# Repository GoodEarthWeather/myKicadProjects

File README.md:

# myKicadProjects
 Kicad Schematic and PCB Projects

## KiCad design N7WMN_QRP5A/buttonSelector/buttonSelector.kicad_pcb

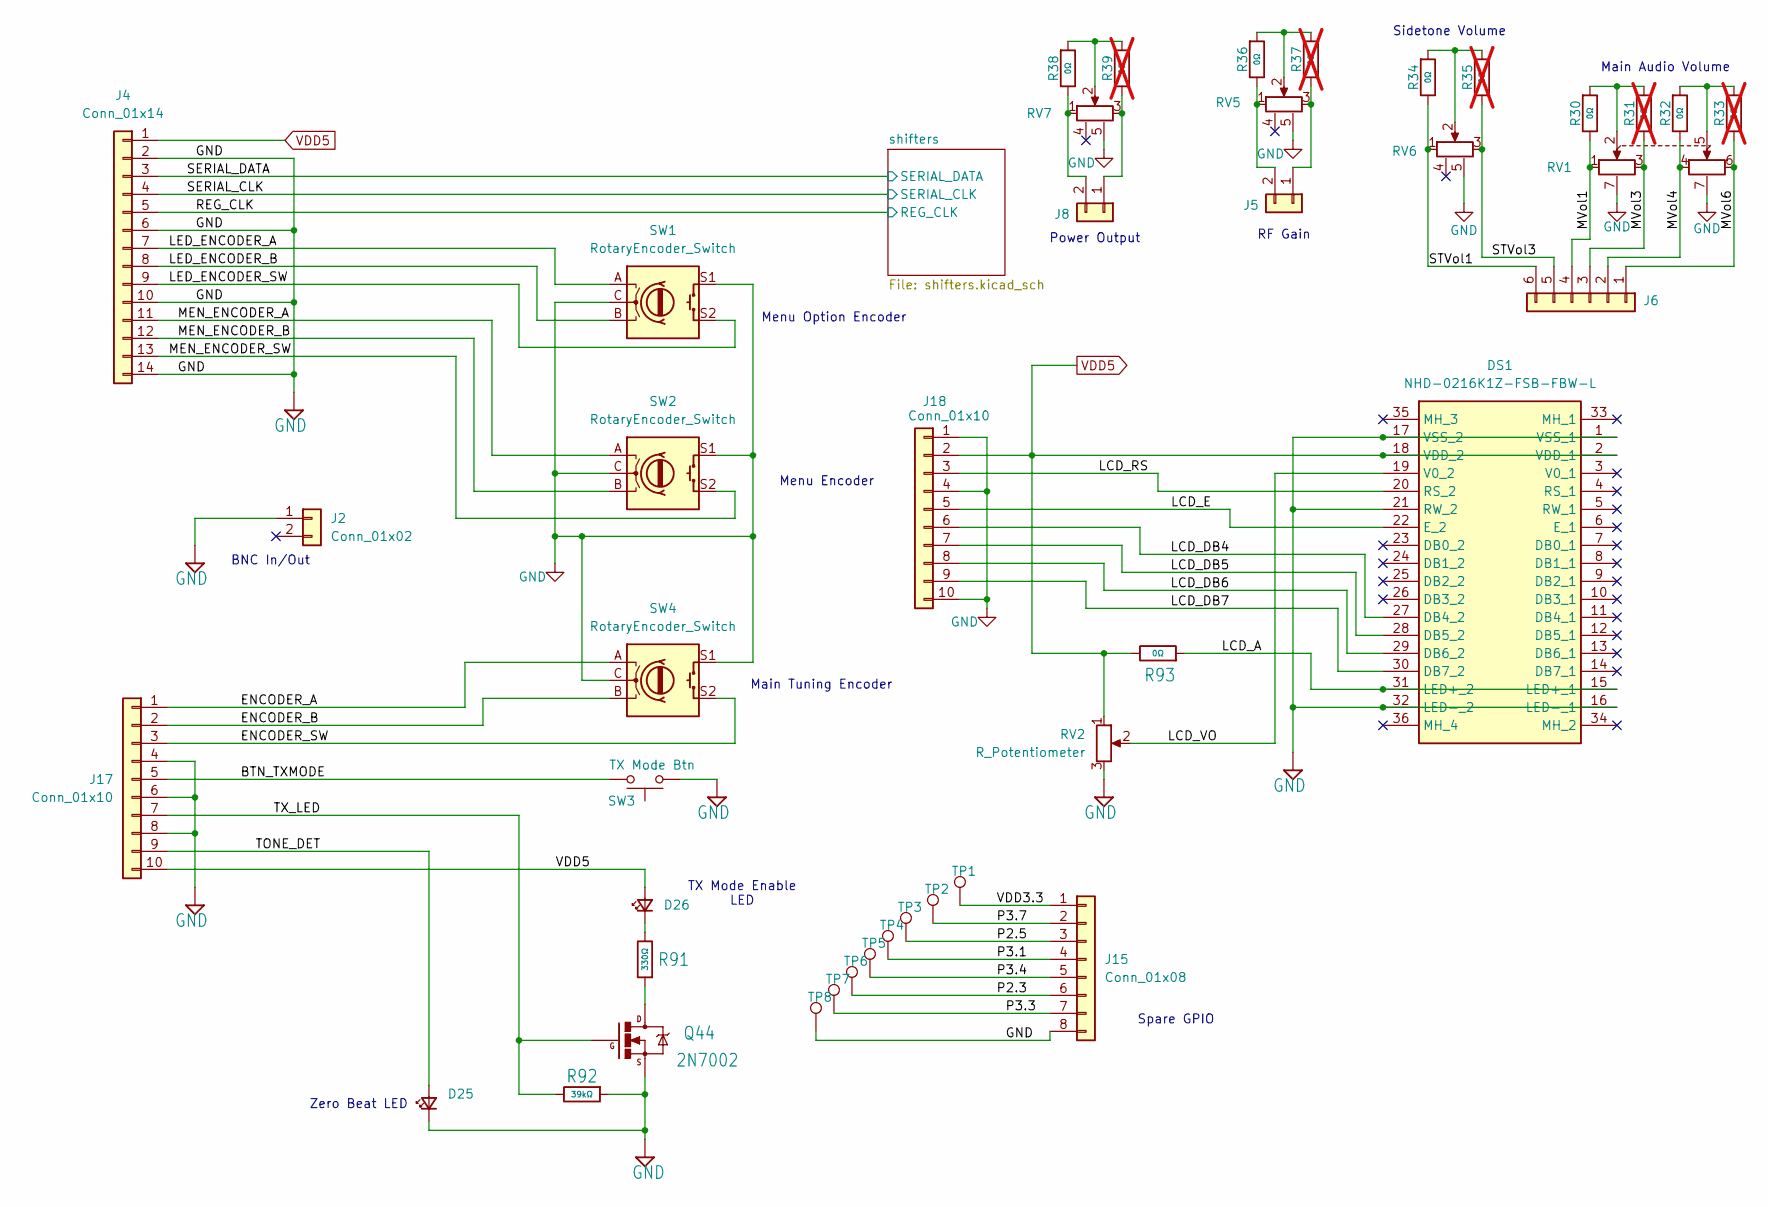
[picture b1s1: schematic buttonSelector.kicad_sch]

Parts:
D25, D26: LED_Small; LED_D5.0mm; MouserPN 606-CMD333URC2
DS1: NHD-0216K1Z-FSB-FBW-L; NHD0216K1ZFSBFBWL; Mouser Part Number 763-0216K1Z-FSB-FBW
J2, J5, J8: Conn_01x02; PinHeader_1x02_P2.54mm_Vertical
J4: Conn_01x14; PinHeader_1x14_P2.54mm_Vertical
J6: Conn_01x06; PinHeader_1x06_P2.54mm_Vertical
J15: Conn_01x08; PinHeader_1x08_P2.54mm_Vertical
J17, J18: Conn_01x10; PinHeader_1x10_P2.54mm_Vertical
Q44: 2N7002; SOT-23; JLCPCB C65189
R30, R32, R34, R36, R38, R93: 0Ω; R_0603; Overload Voltage (Max) 75V; Tolerance ±1%; Part 0603WAF0000T5E; LCSC C21189
R31, R33, R35, R37, R39: 0Ω; R_0603; Overload Voltage (Max) 75V; Tolerance ±1%; Part 0603WAF0000T5E; LCSC C21189; not fitted
R91: 330Ω; R_0603; Overload Voltage (Max) 75V; Tolerance ±1%; Part 0603WAF3300T5E; LCSC C23138
R92: 39kΩ; R_0603; Overload Voltage (Max) 75V; Tolerance ±1%; Part 0603WAF3902T5E; LCSC C23153
RV1: R_Potentiometer_Dual; PVT112-4_Potentiometer; Mouser Part Number 652-PTV112-4420AA103
RV2: R_Potentiometer; Potentiometer_Bourns_3386C_Horizontal
RV5: R_Potentiometer_PVT111; PVT111-4_Potentiometer; Mouser Part Number 652-PTV111-4420AB503
RV6: R_Potentiometer_PVT111; PVT111-4_Potentiometer; Mouser Part Number 652-PTV111-4420AA502
RV7: R_Potentiometer_PVT111; PVT111-4_Potentiometer; Mouser Part Number 652-PTV111-4420AB502
SW1, SW2: RotaryEncoder_Switch; RotaryEncoder_Alps_EC11E-Switch_Vertical_H20mm; Mouser Part Number 652-PEC11R-4220F-S24
SW3: TX Mode Btn; SW_PUSH-12mm
SW4: RotaryEncoder_Switch; RotaryEncoder_Alps_EC11E-Switch_Vertical_H20mm; Mouser Part Number 652-PEC11R-4020F-S24
TP1, TP2, TP3, TP4, TP5, TP6, TP7, TP8: TestPoint; TestPoint_Loop_D2.50mm_Drill1.0mm

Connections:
/BTN_TXMODE: J17.5, SW3.2
/ENCODER_A: J17.1, SW4.A
/ENCODER_B: J17.2, SW4.B
/ENCODER_SW: J17.3, SW4.S2
/LCD_A: DS1.15 (LED+_1), DS1.31 (LED+_2), R93.1
/LCD_DB4: DS1.27 (DB4_2), J18.6
/LCD_DB5: DS1.28 (DB5_2), J18.7
/LCD_DB6: DS1.29 (DB6_2), J18.8
/LCD_DB7: DS1.30 (DB7_2), J18.9
/LCD_E: DS1.22 (E_2), J18.5
/LCD_RS: DS1.20 (RS_2), J18.3
/LCD_VO: DS1.19 (V0_2), RV2.2
/LED_ENCODER_A: J4.7, SW1.A
/LED_ENCODER_B: J4.8, SW1.B
/LED_ENCODER_SW: J4.9, SW1.S2
/MEN_ENCODER_A: J4.11, SW2.A
/MEN_ENCODER_B: J4.12, SW2.B
/MEN_ENCODER_SW: J4.13, SW2.S2
/MVol1: J6.4, R30.2, RV1.1
/MVol3: J6.3, R31.2, RV1.3
/MVol4: J6.2, R32.2, RV1.4
/MVol6: J6.1, R33.2, RV1.6
/P2.3: J15.6, TP6.1 (1_1)
/P2.5: J15.3, TP3.1 (1_1)
/P3.1: J15.4, TP4.1 (1_1)
/P3.3: J15.7, TP7.1 (1_1)
/P3.4: J15.5, TP5.1 (1_1)
/P3.7: J15.2, TP2.1 (1_1)
/REG_CLK: J4.5; also elsewhere on the board
/SERIAL_CLK: J4.4; also elsewhere on the board
/SERIAL_DATA: J4.3; also elsewhere on the board
/STVol1: J6.6, R34.2, RV6.1
/STVol3: J6.5, R35.2, RV6.3
/TONE_DET: D25.2 (A), J17.9
/TX_LED: J17.7, Q44.1 (G), R92.2
/VDD3.3: J15.1, TP1.1 (1_1)
GND: D25.1 (K), DS1.1 (VSS_1), DS1.16 (LED-_1), DS1.17 (VSS_2), DS1.21 (RW_2), DS1.32 (LED-_2), J2.1 (Pin_1_1), J4.2, J4.6, J4.10, J4.14, J15.8, J17.4, J17.6, J17.8, J18.1, J18.4, J18.10, Q44.2 (S), R92.1, RV1.7 (NC), RV2.3, RV5.5 (gnd), RV6.5 (gnd), RV7.5 (gnd), SW1.C, SW1.S1, SW2.C, SW2.S1, SW3.1, SW4.C, SW4.S1, TP8.1 (1_1); also elsewhere on the board
unnamed: D26.1 (K), R91.2
unnamed: J5.1, R37.2, RV5.3
unnamed: J5.2, R36.2, RV5.1
unnamed: J8.1, R39.2, RV7.3
unnamed: J8.2, R38.2, RV7.1
unnamed: Q44.3 (D), R91.1
unnamed: R30.1, R31.1, RV1.2
unnamed: R32.1, R33.1, RV1.5
unnamed: R34.1, R35.1, RV6.2
unnamed: R36.1, R37.1, RV5.2
unnamed: R38.1, R39.1, RV7.2
VDD5: D26.2 (A), DS1.2 (VDD_1), DS1.18 (VDD_2), J4.1, J17.10, J18.2, R93.2, RV2.1; also elsewhere on the board

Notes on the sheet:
Main Tuning Encoder
Menu Encoder
Menu Option Encoder
BNC In/Out
Sidetone Volume
RF Gain
Main Audio Volume
TX Mode Enable LED
Power Output
Spare GPIO
Zero Beat LED

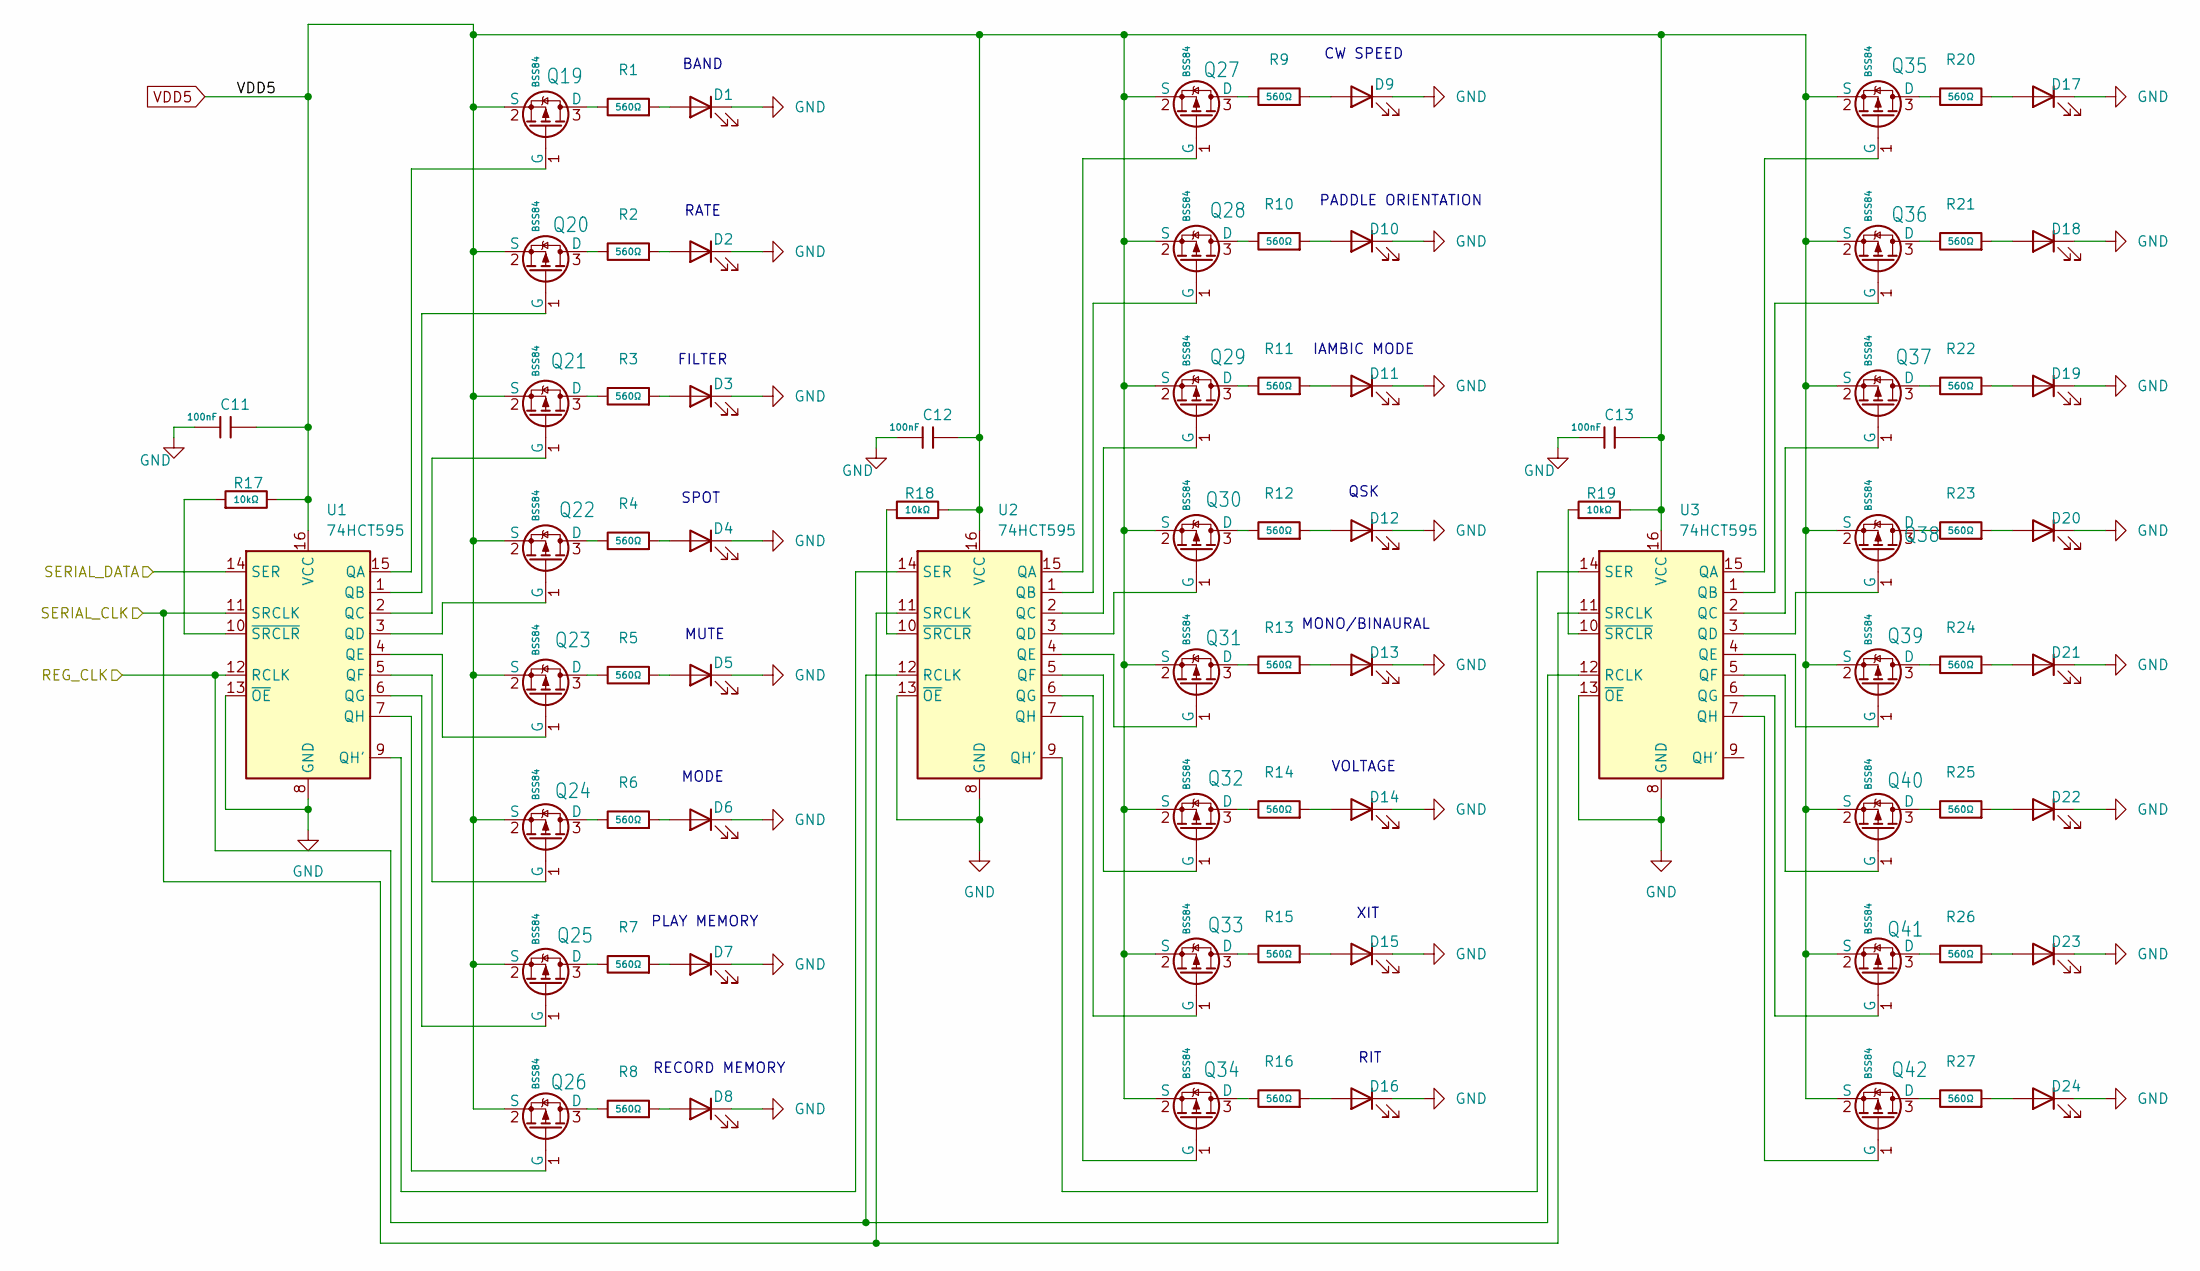
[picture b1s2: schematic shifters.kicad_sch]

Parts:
C11, C12, C13: 100nF; C_0603; Voltage Rated 50V; Tolerance ±10%; Part CC0603KRX7R9BB104; LCSC C14663
D1, D2, D3, D4, D5, D6, D7, D8, D9, D10, D11, D12, D13, D14, D15, D16, D17, D18, D19, D20, D21, D22, D23, D24: LED; LED_D5.0mm_Clear; Mouser Part Number 606-CMD333URC2
Q19, Q20, Q21, Q22, Q23, Q24, Q25, Q26, Q27, Q28, Q29, Q30, Q31, Q32, Q33, Q34, Q35, Q36, Q37, Q38, Q39, Q40, Q41, Q42: BSS84; Q_SOT-23; Part BSS84; JLCPCB C65189
R1, R2, R3, R4, R5, R6, R7, R8, R9, R10, R11, R12, R13, R14, R15, R16, R20, R21, R22, R23, R24, R25, R26, R27: 560Ω; R_0603; Overload Voltage (Max) 75V; Tolerance ±1%; Part 0603WAF5600T5E; JLCPCB C23204
R17, R18, R19: 10kΩ; R_0603; Overload Voltage (Max) 75V; Tolerance ±1%; Part 0603WAF1002T5E; LCSC C25804
U1, U2, U3: 74HCT595; TSSOP-16_4.4x5mm_P0.65mm; JLCPCB C3304571

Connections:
/REG_CLK: U1.12 (RCLK), U2.12 (RCLK), U3.12 (RCLK); also elsewhere on the board
/SERIAL_CLK: U1.11 (SRCLK), U2.11 (SRCLK), U3.11 (SRCLK); also elsewhere on the board
/SERIAL_DATA: U1.14 (SER); also elsewhere on the board
GND: C11.2, C12.2, C13.2, D1.1 (K), D2.1 (K), D3.1 (K), D4.1 (K), D5.1 (K), D6.1 (K), D7.1 (K), D8.1 (K), D9.1 (K), D10.1 (K), D11.1 (K), D12.1 (K), D13.1 (K), D14.1 (K), D15.1 (K), D16.1 (K), D17.1 (K), D18.1 (K), D19.1 (K), D20.1 (K), D21.1 (K), D22.1 (K), D23.1 (K), D24.1 (K), U1.8 (GND), U1.13 (~OE), U2.8 (GND), U2.13 (~OE), U3.8 (GND), U3.13 (~OE); also elsewhere on the board
unnamed: D1.2 (A), R1.1
unnamed: D2.2 (A), R2.1
unnamed: D3.2 (A), R3.1
unnamed: D4.2 (A), R4.1
unnamed: D5.2 (A), R5.1
unnamed: D6.2 (A), R6.1
unnamed: D7.2 (A), R7.1
unnamed: D8.2 (A), R8.1
unnamed: D9.2 (A), R9.1
unnamed: D10.2 (A), R10.1
unnamed: D11.2 (A), R11.1
unnamed: D12.2 (A), R12.1
unnamed: D13.2 (A), R13.1
unnamed: D14.2 (A), R14.1
unnamed: D15.2 (A), R15.1
unnamed: D16.2 (A), R16.1
unnamed: D17.2 (A), R20.1
unnamed: D18.2 (A), R21.1
unnamed: D19.2 (A), R22.1
unnamed: D20.2 (A), R23.1
unnamed: D21.2 (A), R24.1
unnamed: D22.2 (A), R25.1
unnamed: D23.2 (A), R26.1
unnamed: D24.2 (A), R27.1
unnamed: Q19.3 (D), R1.2
unnamed: Q19.1 (G), U1.15 (QA)
unnamed: Q20.3 (D), R2.2
unnamed: Q20.1 (G), U1.1 (QB)
unnamed: Q21.3 (D), R3.2
unnamed: Q21.1 (G), U1.2 (QC)
unnamed: Q22.3 (D), R4.2
unnamed: Q22.1 (G), U1.3 (QD)
unnamed: Q23.3 (D), R5.2
unnamed: Q23.1 (G), U1.4 (QE)
unnamed: Q24.3 (D), R6.2
unnamed: Q24.1 (G), U1.5 (QF)
unnamed: Q25.3 (D), R7.2
unnamed: Q25.1 (G), U1.6 (QG)
unnamed: Q26.3 (D), R8.2
unnamed: Q26.1 (G), U1.7 (QH)
unnamed: Q27.3 (D), R9.2
unnamed: Q27.1 (G), U2.15 (QA)
unnamed: Q28.3 (D), R10.2
unnamed: Q28.1 (G), U2.1 (QB)
unnamed: Q29.3 (D), R11.2
unnamed: Q29.1 (G), U2.2 (QC)
unnamed: Q30.3 (D), R12.2
unnamed: Q30.1 (G), U2.3 (QD)
unnamed: Q31.3 (D), R13.2
unnamed: Q31.1 (G), U2.4 (QE)
unnamed: Q32.3 (D), R14.2
unnamed: Q32.1 (G), U2.5 (QF)
unnamed: Q33.3 (D), R15.2
unnamed: Q33.1 (G), U2.6 (QG)
unnamed: Q34.3 (D), R16.2
unnamed: Q34.1 (G), U2.7 (QH)
unnamed: Q35.3 (D), R20.2
unnamed: Q35.1 (G), U3.15 (QA)
unnamed: Q36.3 (D), R21.2
unnamed: Q36.1 (G), U3.1 (QB)
unnamed: Q37.3 (D), R22.2
unnamed: Q37.1 (G), U3.2 (QC)
unnamed: Q38.3 (D), R23.2
unnamed: Q38.1 (G), U3.3 (QD)
unnamed: Q39.3 (D), R24.2
unnamed: Q39.1 (G), U3.4 (QE)
unnamed: Q40.3 (D), R25.2
unnamed: Q40.1 (G), U3.5 (QF)
unnamed: Q41.3 (D), R26.2
unnamed: Q41.1 (G), U3.6 (QG)
unnamed: Q42.3 (D), R27.2
unnamed: Q42.1 (G), U3.7 (QH)
unnamed: U1.9 (QH'), U2.14 (SER)
unnamed: R17.1, U1.10 (~SRCLR)
unnamed: U2.9 (QH'), U3.14 (SER)
unnamed: R18.1, U2.10 (~SRCLR)
unnamed: R19.1, U3.10 (~SRCLR)
VDD5: C11.1, C12.1, C13.1, Q19.2 (S), Q20.2 (S), Q21.2 (S), Q22.2 (S), Q23.2 (S), Q24.2 (S), Q25.2 (S), Q26.2 (S), Q27.2 (S), Q28.2 (S), Q29.2 (S), Q30.2 (S), Q31.2 (S), Q32.2 (S), Q33.2 (S), Q34.2 (S), Q35.2 (S), Q36.2 (S), Q37.2 (S), Q38.2 (S), Q39.2 (S), Q40.2 (S), Q41.2 (S), Q42.2 (S), R17.2, R18.2, R19.2, U1.16 (VCC), U2.16 (VCC), U3.16 (VCC); also elsewhere on the board

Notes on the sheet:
MONO/BINAURAL
PLAY MEMORY
MUTE
QSK
RECORD MEMORY
SPOT
VOLTAGE
FILTER
BAND
RATE
IAMBIC MODE
RIT
MODE
PADDLE ORIENTATION
XIT
CW SPEED

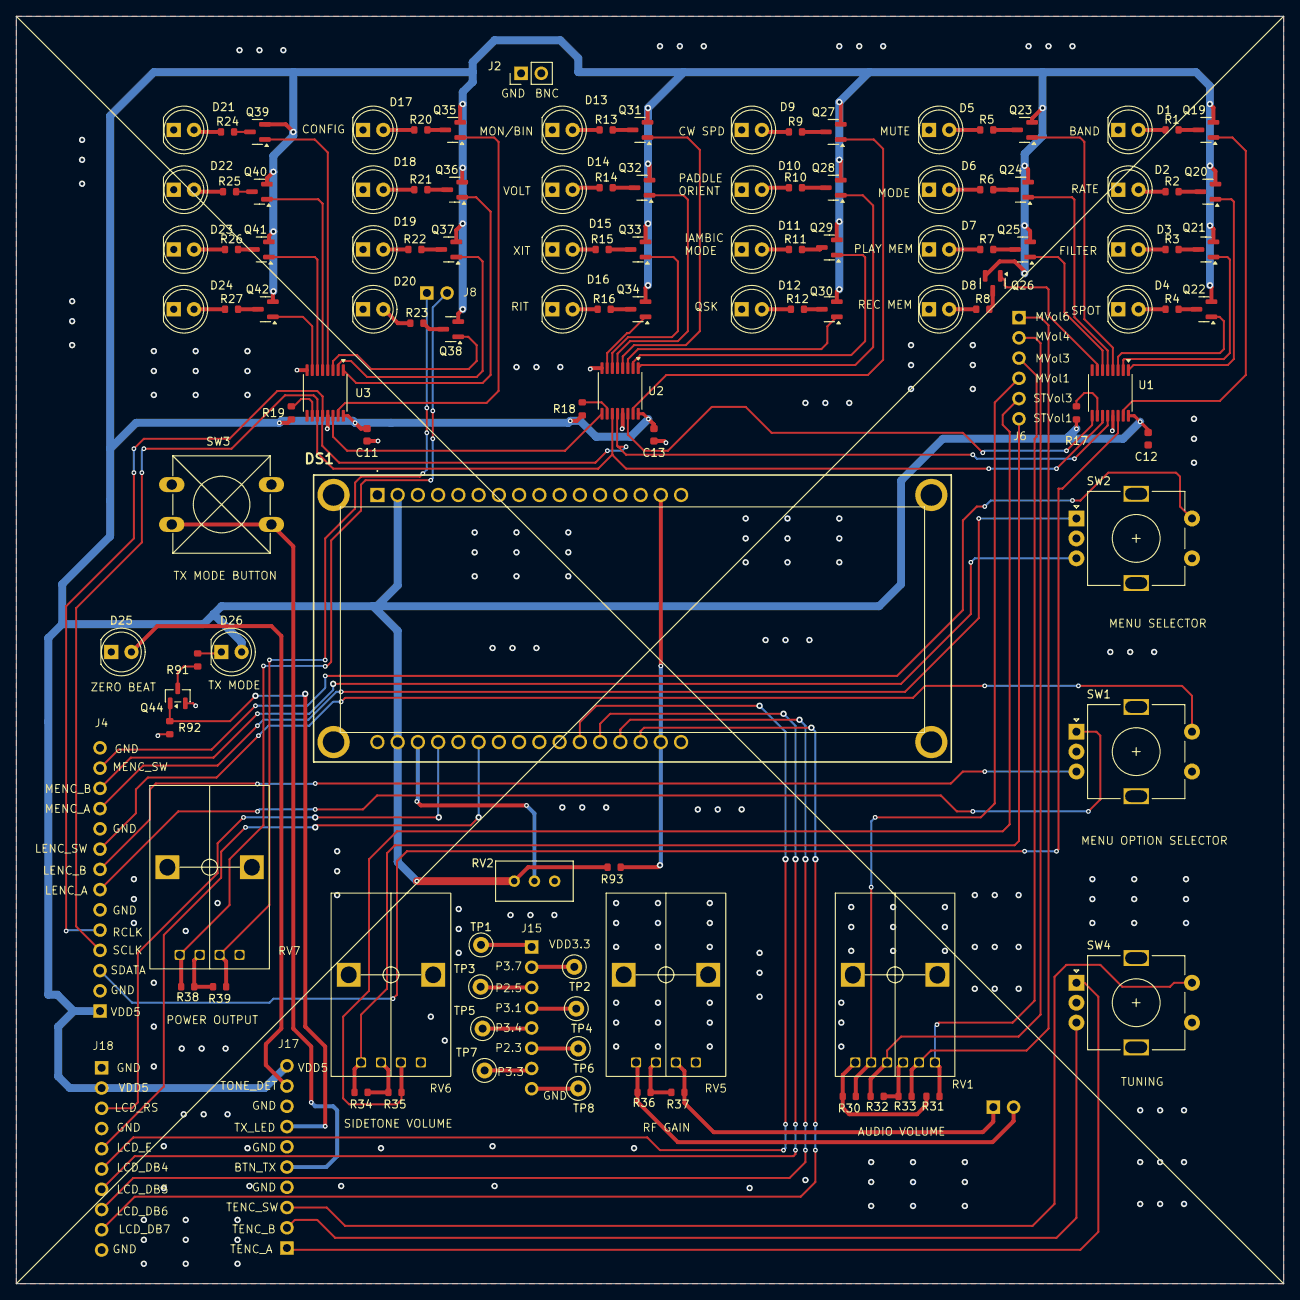
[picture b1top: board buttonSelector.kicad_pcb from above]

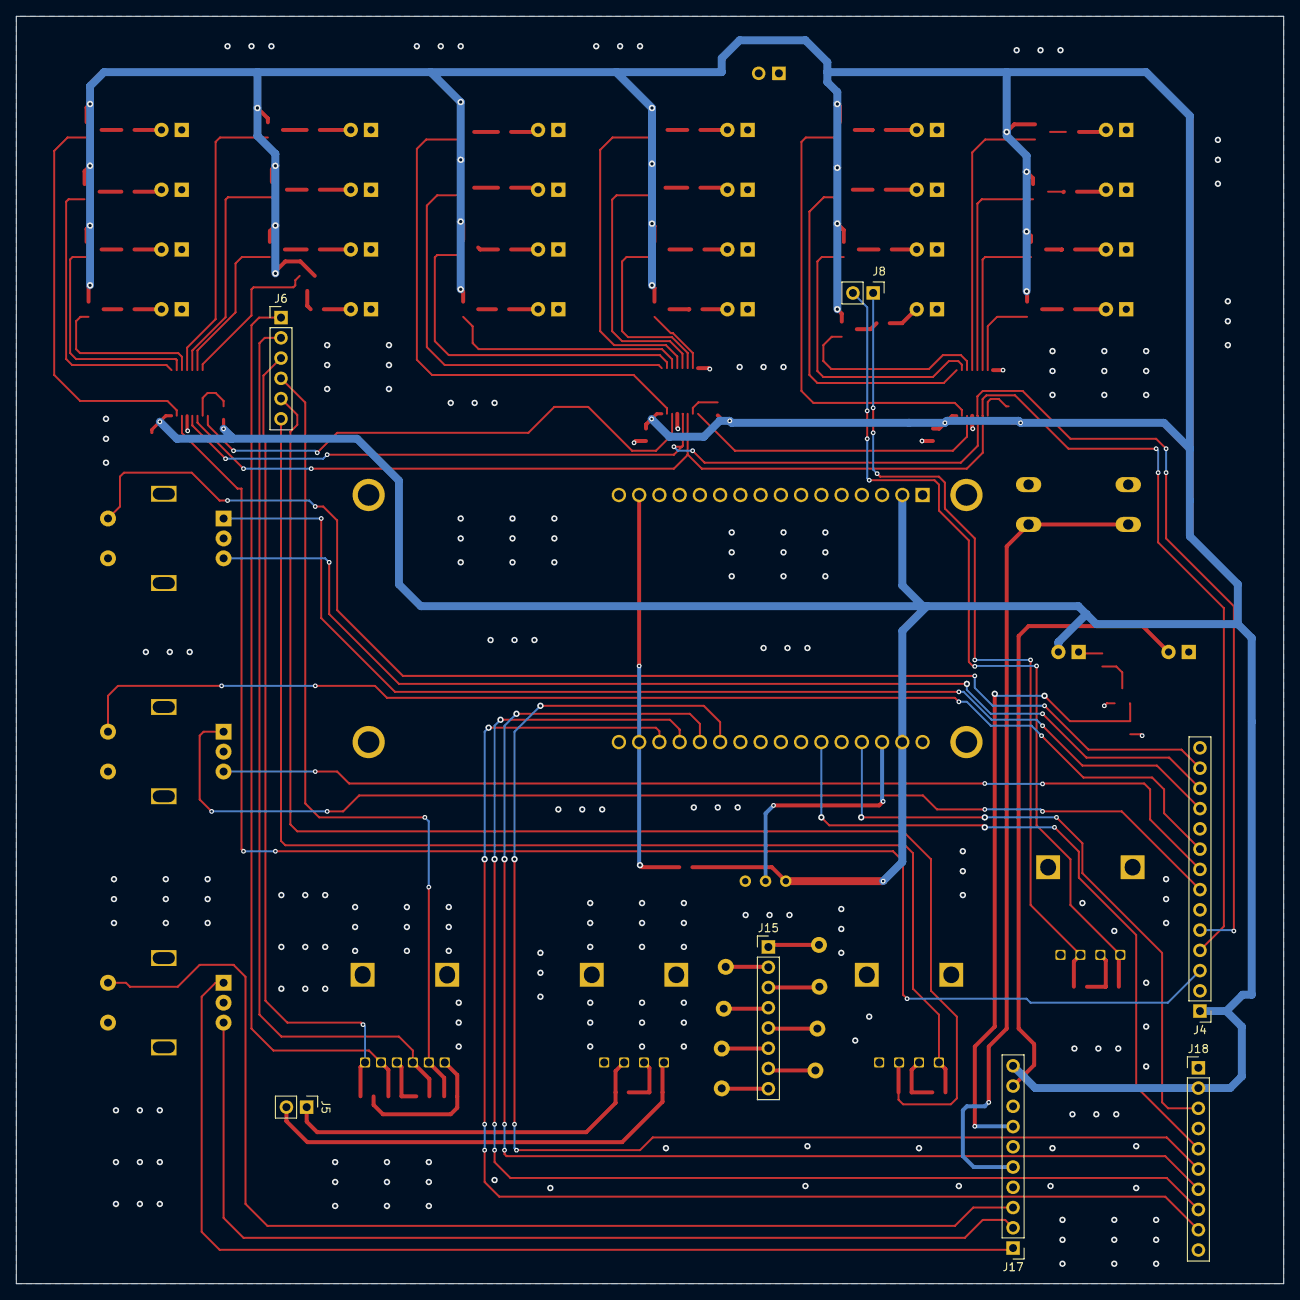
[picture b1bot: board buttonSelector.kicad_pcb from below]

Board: 2 copper layers, 159.0 x 159.0 mm, 123 parts (7 on the bottom side), 126 nets.

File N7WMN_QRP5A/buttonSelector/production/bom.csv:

Designator,Footprint,Quantity,Value,LCSC Part #
"C11, C12, C13",C_0603,3,100nF,C14663
"Q19, Q20, Q21, Q22, Q23, Q24, Q25, Q26, Q27, Q28, Q29, Q30, Q31, Q32, Q33, Q34, Q35, Q36, Q37, Q38, Q39, Q40, Q41, Q42",Q_SOT-23,24,BSS84,C7420340
Q44,SOT-23,1,2N7002,C65189
"R1, R10, R11, R12, R13, R14, R15, R16, R2, R20, R21, R22, R23, R24, R25, R26, R27, R3, R4, R5, R6, R7, R8, R9",R_0603,24,560Ω,C23204
"R17, R18, R19",R_0603,3,10kΩ,C25804
"R30, R31, R32, R33, R34, R35, R36, R37, R38, R39, R93",R_0603,11,0Ω,C21189
R91,R_0603,1,330Ω,C23138
R92,R_0603,1,39kΩ,C23153
"U1, U2, U3",TSSOP-16_4.4x5mm_P0.65mm,3,74HCT595,C3304571

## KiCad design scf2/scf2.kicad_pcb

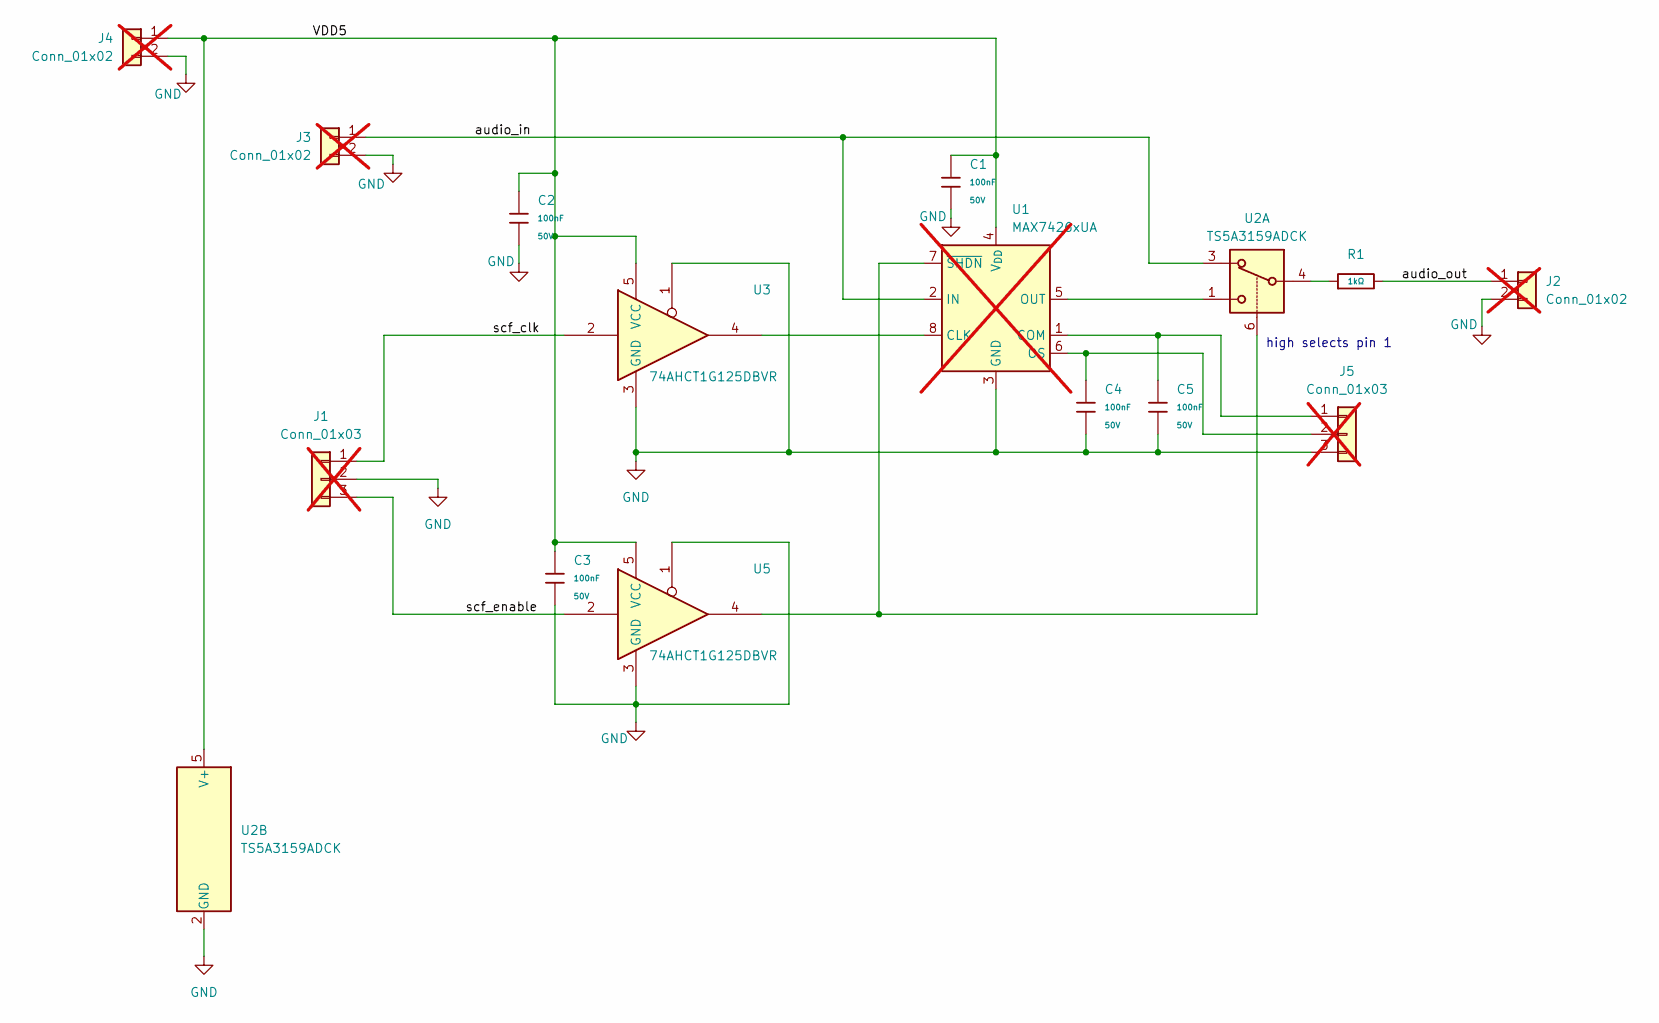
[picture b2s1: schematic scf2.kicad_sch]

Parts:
C1, C2, C3, C4, C5: 100nF; C_0603; Voltage Rated 50V; Tolerance ±10%; Part CC0603KRX7R9BB104; LCSC C14663
J1, J5: Conn_01x03; PinHeader_1x03_P2.54mm_Vertical; not fitted
J2, J3, J4: Conn_01x02; PinHeader_1x02_P2.54mm_Vertical; not fitted
R1: 1kΩ; R_0603; Overload Voltage (Max) 75V; Tolerance ±1%; Part 0603WAF1001T5E; LCSC C21190
U1: MAX7426xUA; MSOP-8_3x3mm_P0.65mm; jlcpcb C17445855; not fitted
U2: TS5A3159ADCK; SOT-363_SC-70-6; jlcpcb C475493
U3, U5: 74AHCT1G125DBVR; SOT-23-5_HandSoldering; jlcpcb C7484

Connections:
/VDD5: C1.1, C2.1, C3.1, J4.1, U1.4 (V_{DD}), U2.5 (V+), U3.5 (VCC), U5.5 (VCC)
/audio_in: J3.1, U1.2 (IN), U2.3
/audio_out: J2.1, R1.2
/scf_clk: J1.1, U3.2
/scf_enable: J1.3, U5.2
GND: C1.2, C2.2, C3.2, C4.2, C5.2, J1.2, J2.2, J3.2, J4.2, J5.3, U1.3 (GND), U2.2 (GND), U3.1, U3.3 (GND), U5.1, U5.3 (GND)
unnamed: C5.1, J5.1, U1.1 (COM)
unnamed: C4.1, J5.2, U1.6 (OS)
unnamed: R1.1, U2.4
unnamed: U1.8 (CLK), U3.4
unnamed: U1.5 (OUT), U2.1
unnamed: U1.7 (~SHDN), U2.6, U5.4

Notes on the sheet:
high selects pin 1

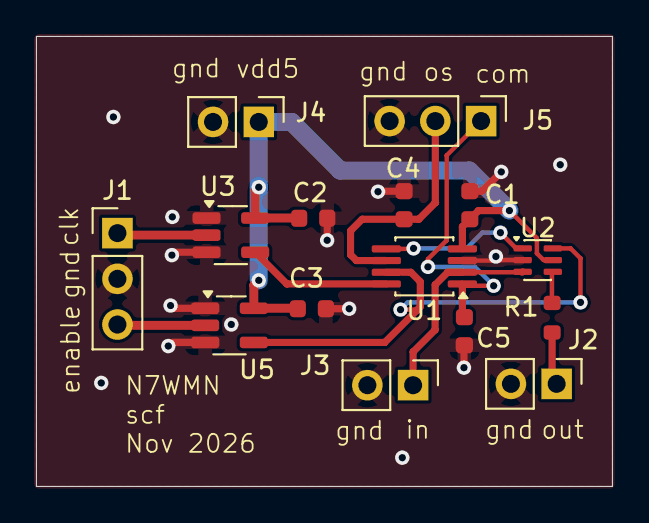
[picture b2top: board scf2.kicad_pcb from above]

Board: 2 copper layers, 32.0 x 25.0 mm, 15 parts (0 on the bottom side), 12 nets.

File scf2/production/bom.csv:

Designator,Footprint,Quantity,Value,LCSC Part #
"C1, C2, C3, C4, C5",C_0603,5,100nF,C14663
R1,R_0603,1,1kΩ,C21190
U2,SOT-363_SC-70-6,1,TS5A3159ADCK,C475493
"U3, U5",SOT-23-5_HandSoldering,2,74AHCT1G125DBVR,C7484

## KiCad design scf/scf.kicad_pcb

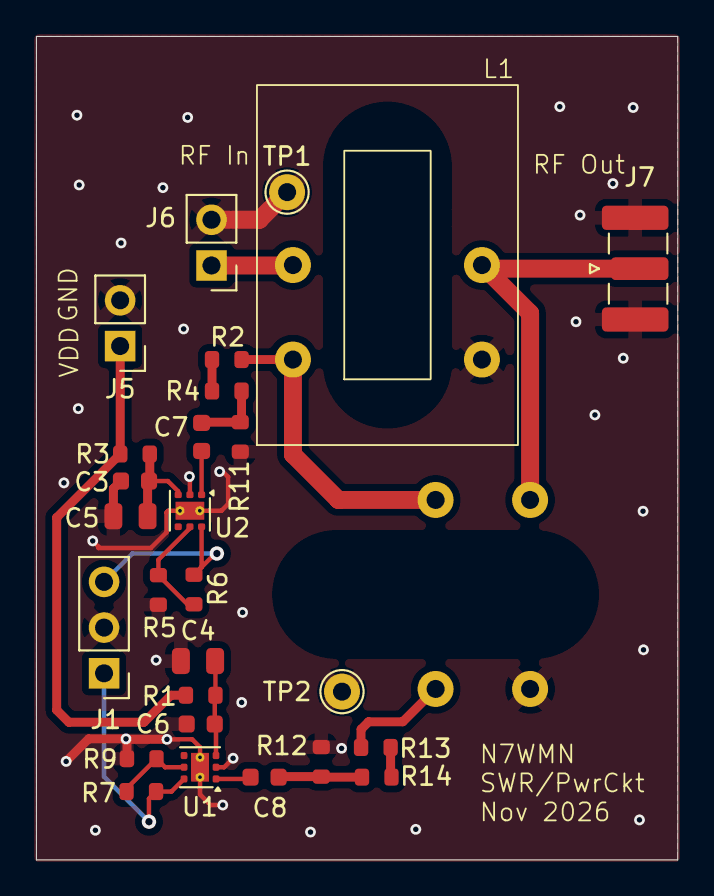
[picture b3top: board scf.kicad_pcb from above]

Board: 2 copper layers, 35.6 x 45.8 mm, 28 parts (1 on the bottom side), 18 nets.

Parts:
C3, C6: 100nF; C_0603
C4, C5: 4.7uF; C_0805
C7, C8: 100pF; C_0603
J1: Conn_01x03; PinHeader_1x03_P2.54mm_Vertical
J5, J6: Conn_01x02; PinHeader_1x02_P2.54mm_Vertical
J7: Conn_Coaxial; SMA_Samtec_SMA-J-P-H-ST-EM1_EdgeMount
L1, L2: L_Iron_Coupled_1243; swrCoupledInductor
R1, R3: 10Ω; R_0603
R2, R4, R13, R14: 15Ω; R_0603
R5, R9: 10kΩ; R_0603
R6, R7: 0Ω; R_0603
R11, R12: 20Ω; R_0603
TP1, TP2: TestPoint; TestPoint_THTPad_D2.0mm_Drill1.0mm
U1, U2: LOG305; WSON-6-1EP_2x2mm_P0.65mm_EP1x1.6mm_ThermalVias

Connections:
/VDD: J5.1, R1.2, R3.1
/rf_in: J6.1, L1.1
/rf_out: J7.1 (In), L1.2, L2.4
/vf: L1.4, L2.1, R2.1
/vf_out: J1.3, R6.1, U2.6 (Log_Out)
/vfdet: C7.1, U2.1 (Log_In)
/vref: L2.2, R13.2
/vref_out: J1.1, R7.1, U1.6 (Log_Out)
/vrefdet: C8.2, U1.1 (Log_In)
GND: C3.2, C4.1, C5.2, C6.1, J1.2, J5.2, J6.2, J7.2 (Ext), L1.3, L2.3, R5.2, R9.2, R11.2, R12.2, TP1.1 (1_1), TP2.1 (1_1), U1.2 (VEE), U1.7 (Pad), U2.2 (VEE), U2.7 (Pad)
unnamed: C7.2, R4.1, R11.1
unnamed: C8.1, R12.1, R14.2
unnamed: R2.2, R4.2
unnamed: R13.1, R14.1
unnamed: R7.2, R9.1, U1.5 (FB)
unnamed: C4.2, C6.2, R1.1, U1.3 (VCC)
unnamed: R5.1, R6.2, U2.5 (FB)
unnamed: C3.1, C5.1, R3.2, U2.3 (VCC)
